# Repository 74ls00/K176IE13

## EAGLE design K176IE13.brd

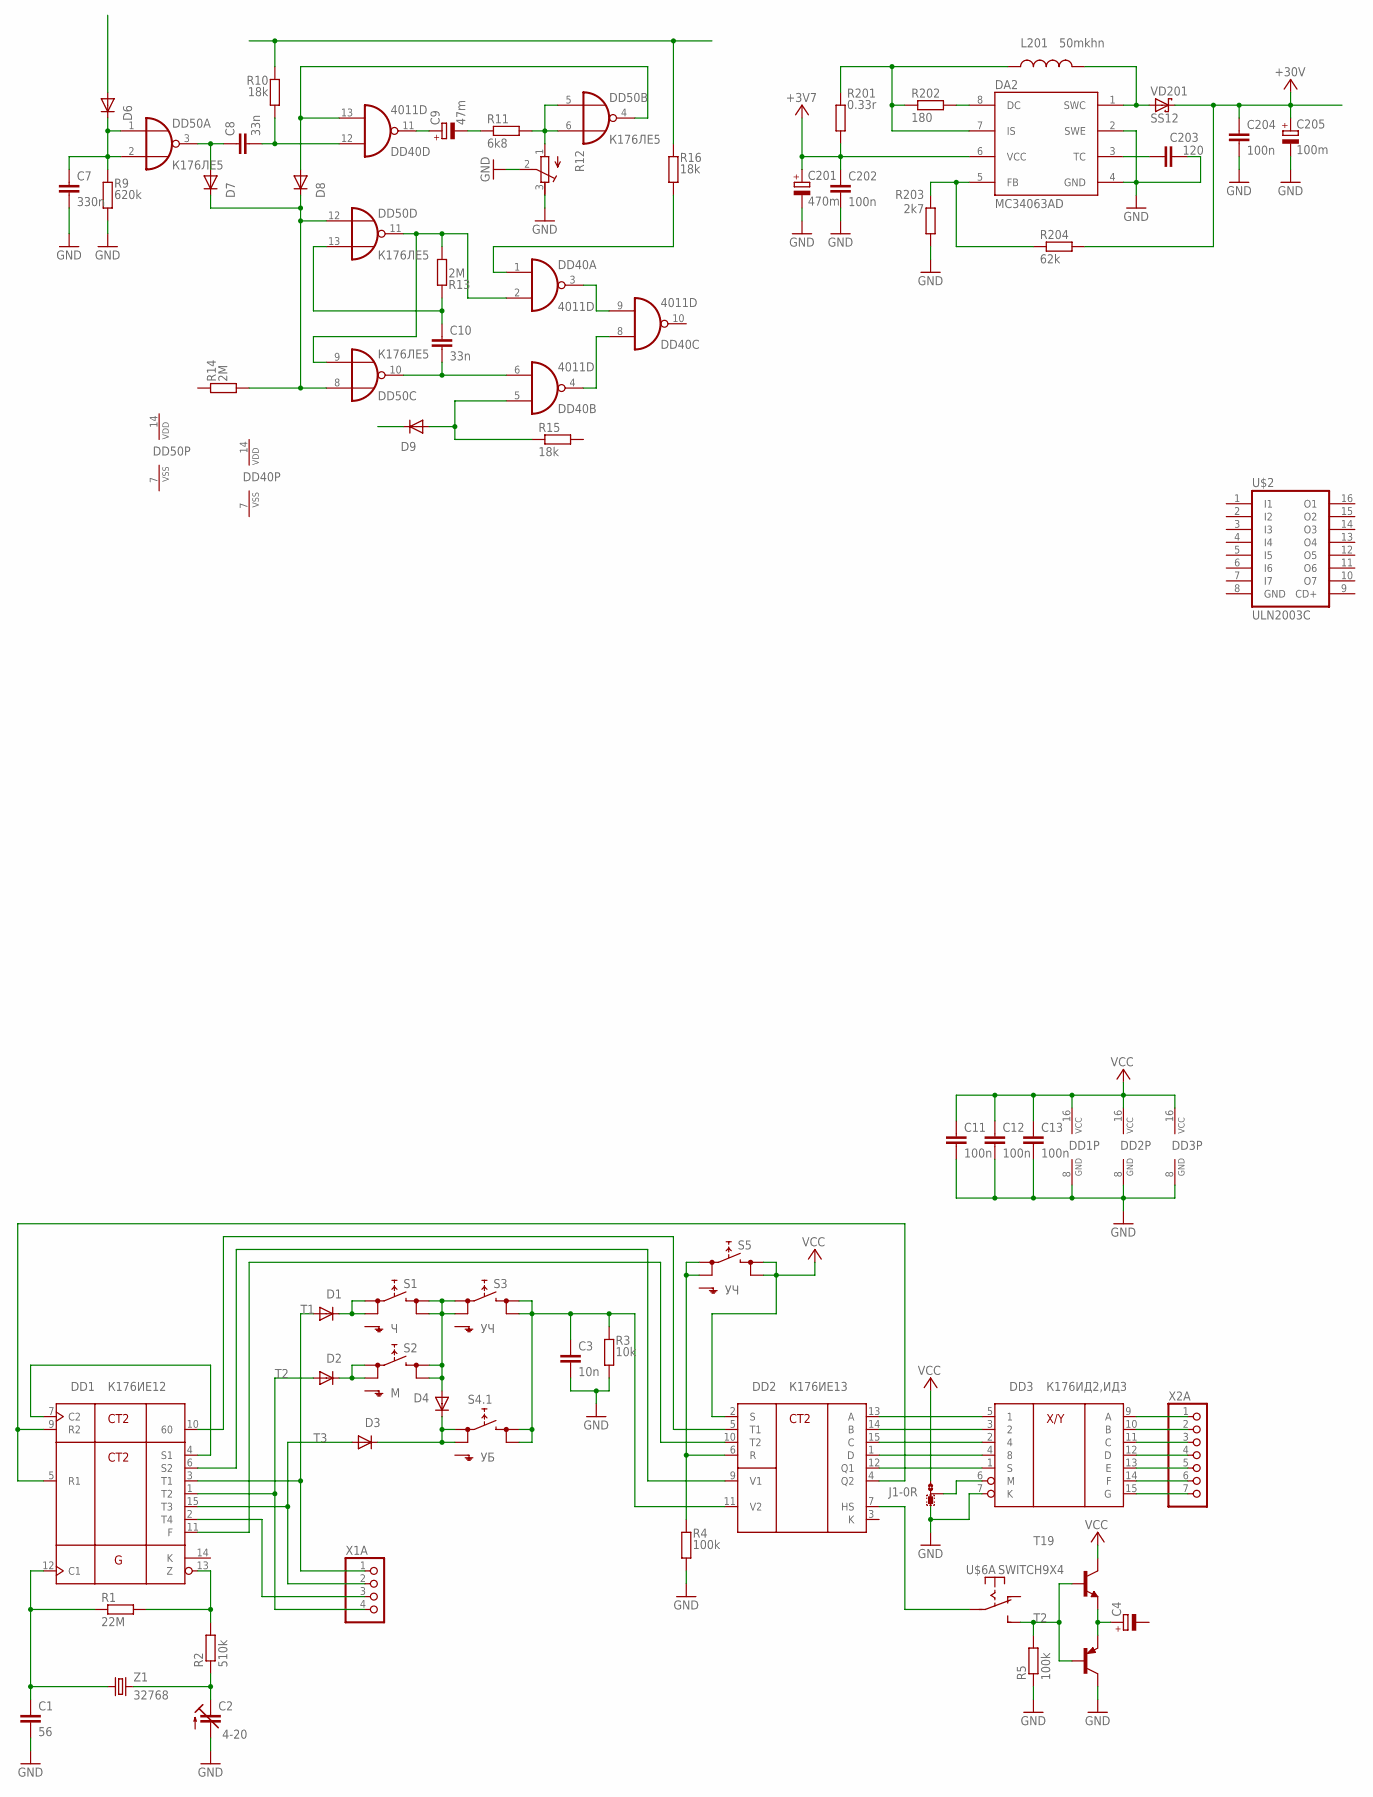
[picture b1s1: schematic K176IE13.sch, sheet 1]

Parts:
C1: 56; C0805
C2: 4-20; CTRIMTZ03
C3: 10n; C0805
C4: CPOL-EUE2.5-5; E2,5-5
C7: 330n; C0805
C8, C10: 33n; C0805
C9: 47m; E2,5-5
C11, C12, C202, C204: 100n; C0805
C13: 100n; C1206
C201: 470m; E3,5-8
C203: 120; C0805
C205: 100m; E2,5-5
D1, D2, D3, D4, D6, D7, D8, D9: DIODE-SOD80C; SOD80C
DA2: MC34063AD; SOIC8
DD1: К176ИЕ12; DIL16B
DD2: К176ИЕ13; DIL16B
DD3: К176ИД2,ИД3; DIL16B
DD40: 4011D; SO14
DD50: К176ЛЕ5; DIL14
J1: 0R-JUMPB; B0R-JMP
L201: 50mkhn; TFI0305
R1: 22M; 0207/10
R2: 510k; M0805
R3: 10k; M0805
R4, R5: 100k; M0805
R9: 620k; M0805
R10, R15, R16: 18k; M0805
R11: 6k8; M0805
R12: R-TRIMM3339P; RTRIM3339P
R13, R14: 2M; M0805
R201: 0.33r; M1206
R202: 180; M0805
R203: 2k7; M0805
R204: 62k; M0805
S1: Ч; SKHMPXE010
S2: М; SKHMPXE010
S3, S5: УЧ; SKHMPXE010
S4.1: УБ; SKHMPXE010
T2: MPSA56-PNP-TO92-BCE; TO92-BCE
T19: -NPN-TO92-ECB; TO92-ECB
U$2: ULN2003C; DIL16_1
U$6: SWITCH9X4
VD201: SS12; SMB
X1A: PINHD-1X4; 1X04
X2A: PINHD-1X7; 1X07
Z1: 32768; FC-12M

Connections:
+3V7: C201.+, C202.1, DA2.6 (VCC), R201.1
+30V: C204.1, C205.+, R204.2, VD201.C; also elsewhere on the board
GND: C1.2, C2.2 (A), C3.2, C7.2, C11.2, C12.2, C13.2, C201.-, C202.2, C203.2, C204.2, C205.-, DA2.2 (SWE), DA2.4 (GND), DD1.8 (GND), DD2.8 (GND), DD3.7 (K), DD3.8 (GND), J1.3, R3.1, R4.1, R5.1, R9.1, R12.2 (S), R12.3 (E), R203.1, T2.C, U$2.8 (GND); also elsewhere on the board
unnamed: C1.1, DD1.12 (C1), R1.1, Z1.P$1 (1)
unnamed: DD1.13 (Z), R1.2, R2.2
unnamed: C2.1 (E), R2.1, Z1.P$2 (2)
unnamed: D2.C, S2.1 (1.1), S2.2 (1.2)
unnamed: DD2.13 (A), DD3.5 (1)
unnamed: DD2.14 (B), DD3.3 (2)
unnamed: DD2.15 (C), DD3.2 (4)
unnamed: DD2.1 (D), DD3.4 (8)
unnamed: D1.C, S1.1 (1.1), S1.2 (1.2)
unnamed: DD2.12 (Q1), DD3.1 (S)
unnamed: DD2.6 (R), R4.2, S5.1 (1.1), S5.2 (1.2)
unnamed: D4.A, S1.3 (2.1), S1.4 (2.2), S2.3 (2.1), S2.4 (2.2), S3.1 (1.1), S3.2 (1.2)
unnamed: D3.C, D4.C, S4.1.1 (1.1), S4.1.2 (1.2)
unnamed: DD1.10 (60), DD2.5 (T1)
unnamed: C3.1, DD2.11 (V2), R3.2, S3.3 (2.1), S3.4 (2.2), S4.1.3 (2.1), S4.1.4 (2.2)
unnamed: DD1.4 (S1), DD1.7 (C2)
unnamed: C4.+, T2.E, T19.E
unnamed: DD3.9 (A), X2A.1
unnamed: DD3.10 (B), X2A.2
unnamed: DD3.11 (C), X2A.3
unnamed: DD3.12 (D), X2A.4
unnamed: DD3.13 (E), X2A.5
unnamed: DD3.14 (F), X2A.6
unnamed: DD3.15 (G), X2A.7
unnamed: DD3.6 (M), J1.2
unnamed: DA2.8 (DC), R202.2
unnamed: DA2.7 (IS), L201.1, R201.2, R202.1
unnamed: DD1.6 (S2), DD2.9 (V1)
unnamed: R5.2, T2.B, T19.B, U$6.12 (S)
unnamed: DD1.11 (F), DD2.10 (T2)
unnamed: DD1.5 (R1), DD1.9 (R2), DD2.4 (Q2)
unnamed: DA2.1 (SWC), L201.2, VD201.A
unnamed: DD2.7 (HS), U$6.10
unnamed: C203.1, DA2.3 (TC)
unnamed: DA2.5 (FB), R203.2, R204.1
unnamed: C7.1, D6.C, DD50.1 (I0), DD50.2 (I1), R9.2
unnamed: D8.A, DD40.13 (I1), DD50.4 (O)
unnamed: C8.1, D7.A, DD50.3 (O)
unnamed: C8.2, DD40.12 (I0), R10.1
unnamed: D7.C, D8.C, DD50.8 (I0), DD50.12 (I0), R14.1
unnamed: C9.+, DD40.11 (O)
unnamed: C9.-, R11.1
unnamed: DD50.5 (I0), DD50.6 (I1), R11.2, R12.1 (A)
unnamed: DD40.3 (O), DD40.9 (I1)
unnamed: DD40.2 (I1), DD50.9 (I1), DD50.11 (O), R13.1
unnamed: C10.1, DD50.13 (I1), R13.2
unnamed: DD40.4 (O), DD40.8 (I0)
unnamed: C10.2, DD40.6 (I1), DD50.10 (O)
unnamed: DD40.1 (I0), R16.1
unnamed: R10.2, R16.2
unnamed: D9.A, DD40.5 (I0), R15.1
T1: D1.A, DD1.3 (T1), X1A.1
T2: D2.A, DD1.1 (T2), X1A.4
T3: D3.A, DD1.15 (T3), X1A.2
T4: DD1.2 (T4), X1A.3
VCC: C11.1, C12.1, C13.1, DD1.16 (VCC), DD2.2 (S), DD2.16 (VCC), DD3.16 (VCC), J1.1, S5.3 (2.1), S5.4 (2.2), T19.C; also elsewhere on the board
VDD: DD40.14 (VDD), DD50.14 (VDD)
VSS: DD40.7 (VSS), DD50.7 (VSS)

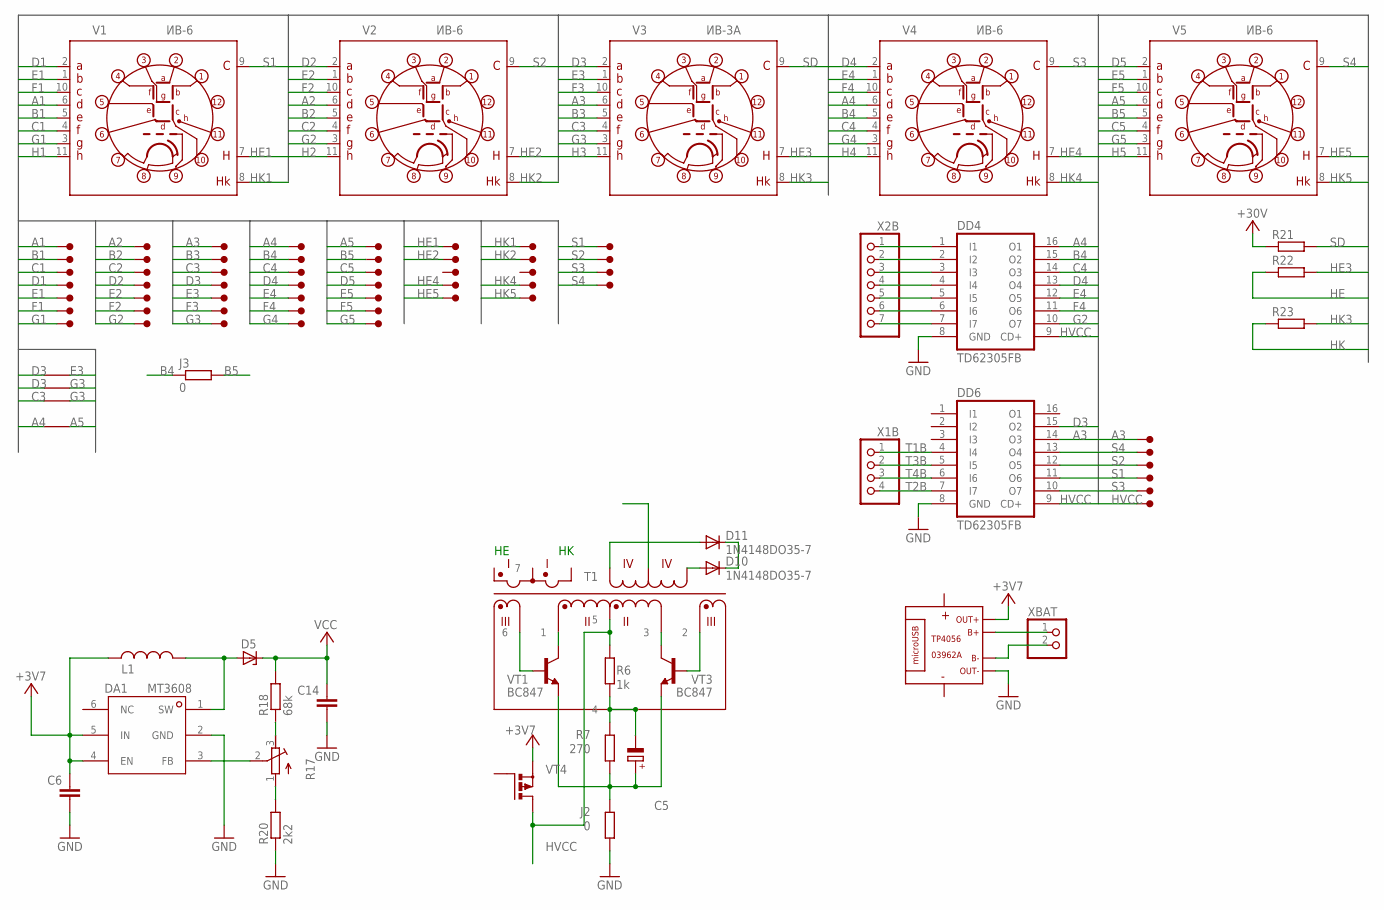
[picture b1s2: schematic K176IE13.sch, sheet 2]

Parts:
C5: CPOL-EUSANYO_SMD_A5; SANYO-OSCON_SMD_A5
C6, C14: C-EUC1206; C1206
D5: ZENER-DIODESMB; SMB
D10, D11: 1N4148DO35-7; DO35-7
DA1: MT3608SOT23-6; SOT23-6
DD4, DD6: TD62305FB; SO16
J2, J3: 0; M1206
L1: L-USL3225M; L3225M
R6: 1k; M0805
R7: 270; M0805
R17: R-TRIMM3296P; RTRIM3296P
R18: 68k; M0805
R20: 2k2; M0805
R21, R22, R23: R-EU_M0805; M0805
T1: TRAN_EE16; EE16
U$3, U$35, U$50, U$67: +
U$4, U$7, U$12, U$13, U$14, U$15, U$17, U$19, U$20, U$22, U$23, U$24, U$25, U$26, U$27, U$28, U$29, U$30, U$31, U$32, U$33, U$34, U$36, U$37, U$38, U$39, U$40, U$41, U$42, U$43, U$44, U$45, U$46, U$47, U$48, U$49, U$51, U$52, U$53, U$54, U$55, U$56, U$57, U$58, U$59, U$60, U$61, U$62, U$63, U$64, U$65, U$66, U$68, U$69, U$70: PAD; PAD-R
U$9: MOD_TP4056; MOD_03962A
V1, V5: ИВ-6; IV-6_VIXC
V2: ИВ-6; IV-6_VIXL
V3: ИВ-3А; IV-3A_VIXC
V4: ИВ-6; IV-6_VIXR
VT1, VT3: BC847; SOT23
VT4: MOSFET-P_SOT23; SOT23
X1B: PINHD-1X4; 1X04
X2B: PINHD-1X7; 1X07
XBAT: PINHD-1X2/2; 1X02

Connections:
+3V3: C6.1, DA1.4 (EN), DA1.5 (IN), L1.2, U$9.P2+OUT, VT4.2 (S)
+30V: R21.1; also elsewhere on the board
A1: U$4.P$1, V1.6 (D)
A2: U$36.P$1, V2.6 (D)
A3: DD6.14 (O3), U$20.P$1, U$55.P$1, V3.6 (D)
A4: DD4.16 (O1), U$43.P$1, U$67.P$1, V4.6 (D)
A5: U$28.P$1, U$67.P$2, V5.6 (D)
B1: U$7.P$1, V1.5 (E)
B2: U$37.P$1, V2.5 (E)
B3: U$22.P$1, V3.5 (E)
B4: DD4.15 (O2), J3.1, U$44.P$1, V4.5 (E)
B5: J3.2, U$29.P$1, V5.5 (E)
C1: U$12.P$1, V1.4 (F)
C2: U$38.P$1, V2.4 (F)
C3: U$23.P$1, U$35.P$1, V3.4 (F)
C4: DD4.14 (O3), U$45.P$1, V4.4 (F)
C5: U$30.P$1, V5.4 (F)
D1: U$14.P$1, V1.2 (A)
D2: U$39.P$1, V2.2 (A)
D3: DD6.15 (O2), U$3.P$1, U$24.P$1, U$50.P$2, V3.2 (A)
D4: DD4.13 (O4), U$46.P$1, V4.2 (A)
D5: U$31.P$1, V5.2 (A)
E1: U$15.P$1, V1.1 (B)
E2: U$40.P$1, V2.1 (B)
E3: U$3.P$2, U$25.P$1, V3.1 (B)
E4: DD4.12 (O5), U$47.P$1, V4.1 (B)
E5: U$32.P$1, V5.1 (B)
F1: U$17.P$1, V1.10 (C)
F2: U$41.P$1, V2.10 (C)
F3: U$26.P$1, V3.10 (C)
F4: DD4.11 (O6), U$48.P$1, V4.10 (C)
F5: U$33.P$1, V5.10 (C)
G1: U$19.P$1, V1.3 (G)
G2: DD4.10 (O7), U$42.P$1, V2.3 (G)
G3: U$27.P$1, U$35.P$2, U$50.P$1, V3.3 (G)
G4: U$49.P$1, V4.3 (G)
G5: U$34.P$1, V5.3 (G)
GND: C6.2, C14.2, DA1.2 (GND), DD4.8 (GND), DD6.8 (GND), J2.1, R20.1, U$9.P2-OUT; also elsewhere on the board
H1: V1.11 (H)
H2: V2.11 (H)
H3: V3.11 (H)
H4: V4.11 (H)
H5: V5.11 (H)
HE: R22.1
HE1: U$51.P$1, V1.7 (H1)
HE2: U$53.P$1, V2.7 (H1)
HE3: R22.2, V3.7 (H1)
HE4: U$64.P$1, V4.7 (H1)
HE5: U$57.P$1, V5.7 (H1)
HK: R23.1
HK1: U$52.P$1, V1.8 (H2K)
HK2: U$54.P$1, V2.8 (H2K)
HK3: R23.2, V3.8 (H2K)
HK4: U$66.P$1, V4.8 (H2K)
HK5: U$56.P$1, V5.8 (H2K)
HVCC: DD4.9 (CD+), DD6.9 (CD+), R6.1, T1.5, U$58.P$1, VT4.3 (D)
unnamed: DD4.4 (I4), X2B.4
unnamed: C5.+, J2.2, R7.1, VT1.2 (E), VT3.2 (E)
unnamed: DD4.1 (I1), X2B.1
unnamed: DD4.2 (I2), X2B.2
unnamed: DD4.3 (I3), X2B.3
unnamed: D5.A, DA1.1 (SW), L1.1
unnamed: R17.3 (E), R18.1
unnamed: DA1.3 (FB), R17.2 (S)
unnamed: R17.1 (A), R20.2
unnamed: U$9.P2+B, XBAT.1
unnamed: U$9.P2-B, XBAT.2
unnamed: DD4.5 (I5), X2B.5
unnamed: DD4.6 (I6), X2B.6
unnamed: DD4.7 (I7), X2B.7
unnamed: D10.C, D11.C
unnamed: T1.1, VT1.3 (C)
unnamed: T1.3, VT3.3 (C)
unnamed: T1.2, VT3.1 (B)
unnamed: T1.6, VT1.1 (B)
unnamed: C5.-, R6.2, R7.2, T1.4
S1: DD6.11 (O6), U$13.P$1, U$60.P$1, V1.9 (S)
S2: DD6.12 (O5), U$61.P$1, U$68.P$1, V2.9 (S)
S3: DD6.10 (O7), U$59.P$1, U$69.P$1, V4.9 (S)
S4: DD6.13 (O4), U$62.P$1, U$70.P$1, V5.9 (S)
SD: R21.2, V3.9 (S)
T1B: DD6.4 (I4), X1B.1
T2B: DD6.7 (I7), X1B.4
T3B: DD6.5 (I5), X1B.2
T4B: DD6.6 (I6), X1B.3
VCC: C14.1, D5.C, R18.2; also elsewhere on the board

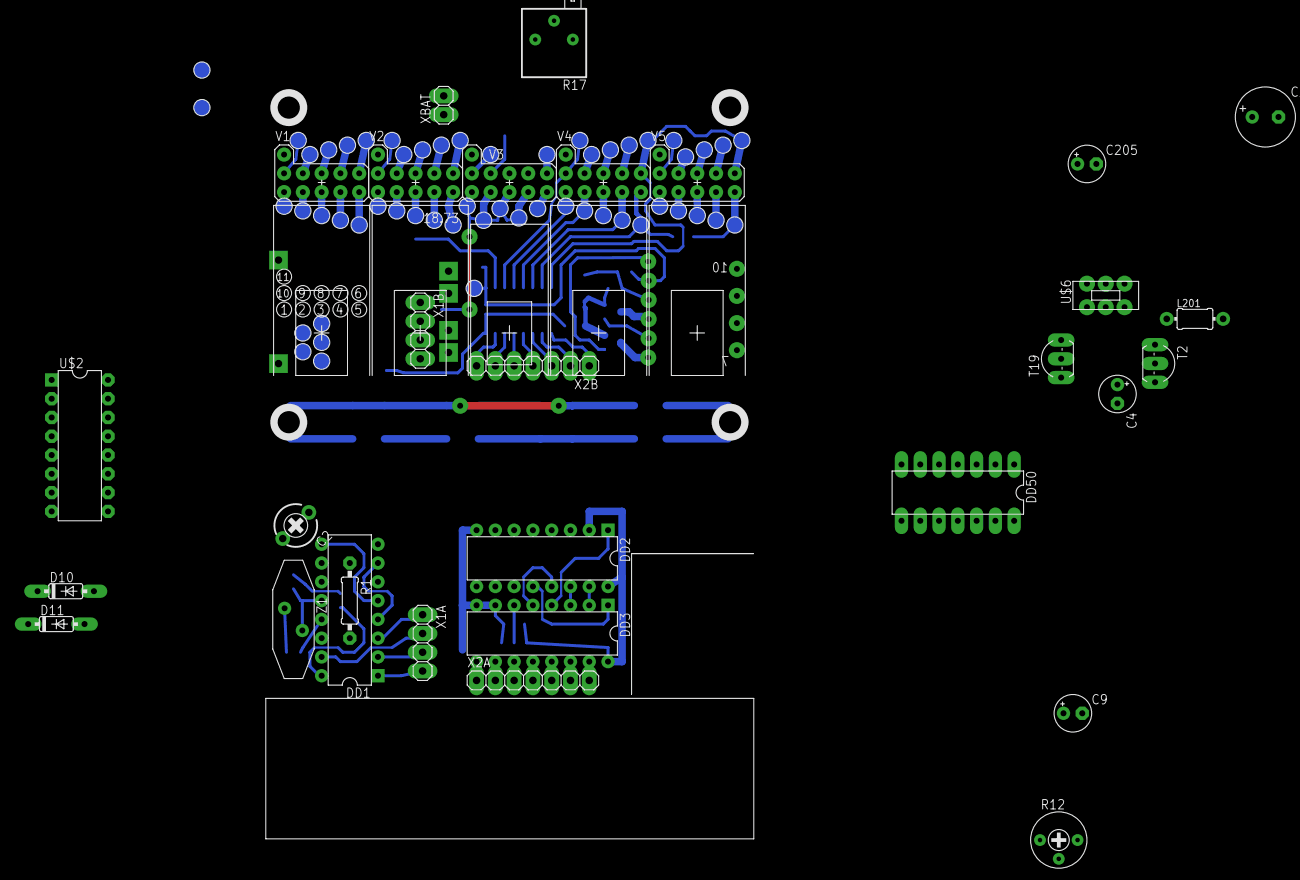
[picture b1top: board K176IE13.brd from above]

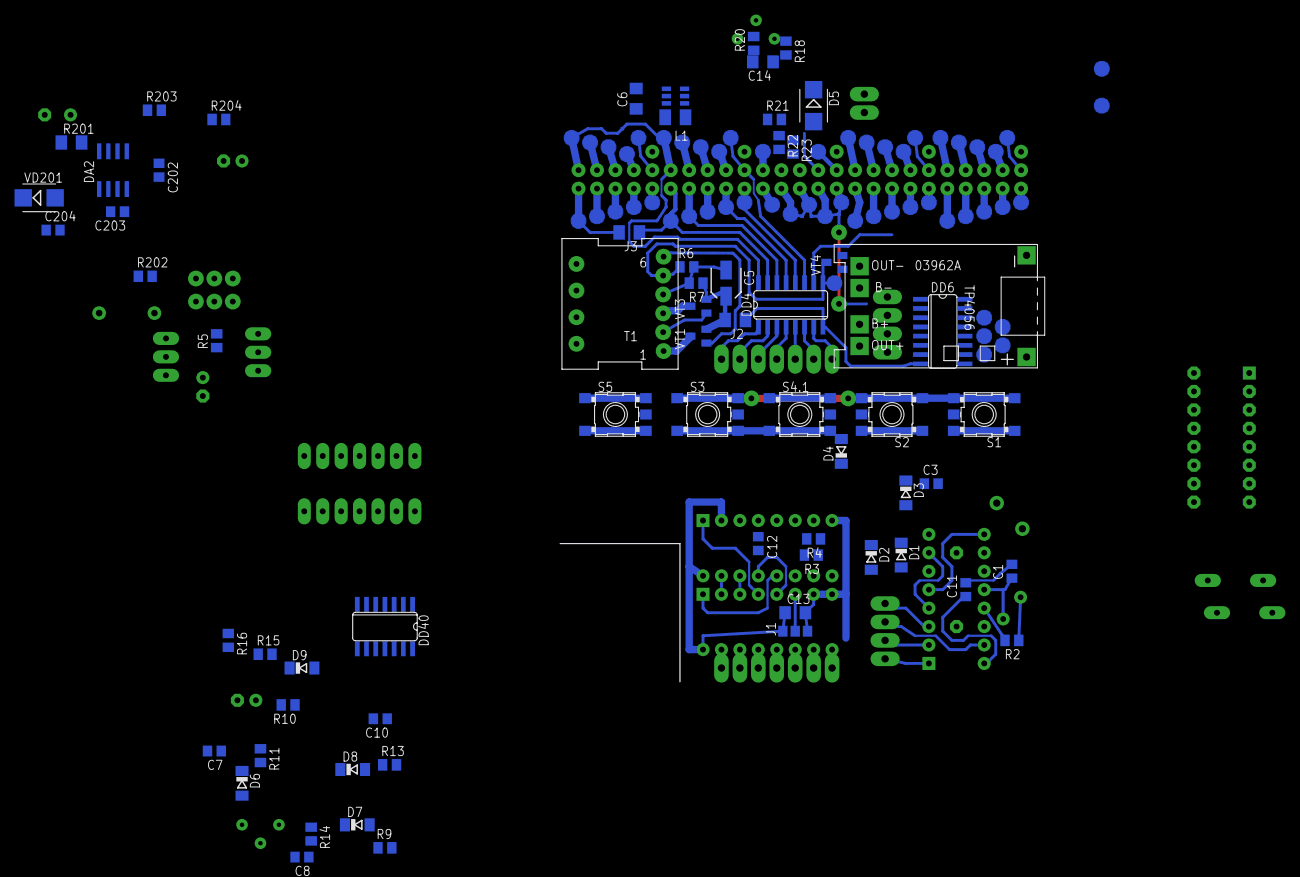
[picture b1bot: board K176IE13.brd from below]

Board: 2 copper layers, 156 parts (69 on the bottom side), 137 nets.

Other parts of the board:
U$5: CON_VFD_SCH
U$11: 1865
